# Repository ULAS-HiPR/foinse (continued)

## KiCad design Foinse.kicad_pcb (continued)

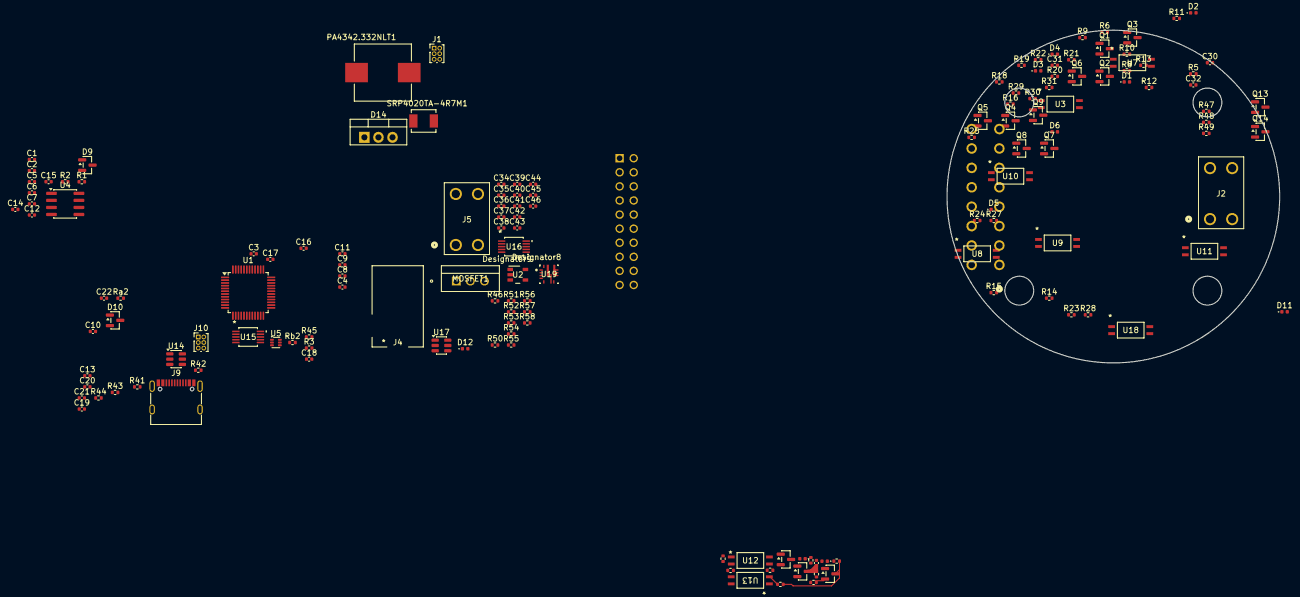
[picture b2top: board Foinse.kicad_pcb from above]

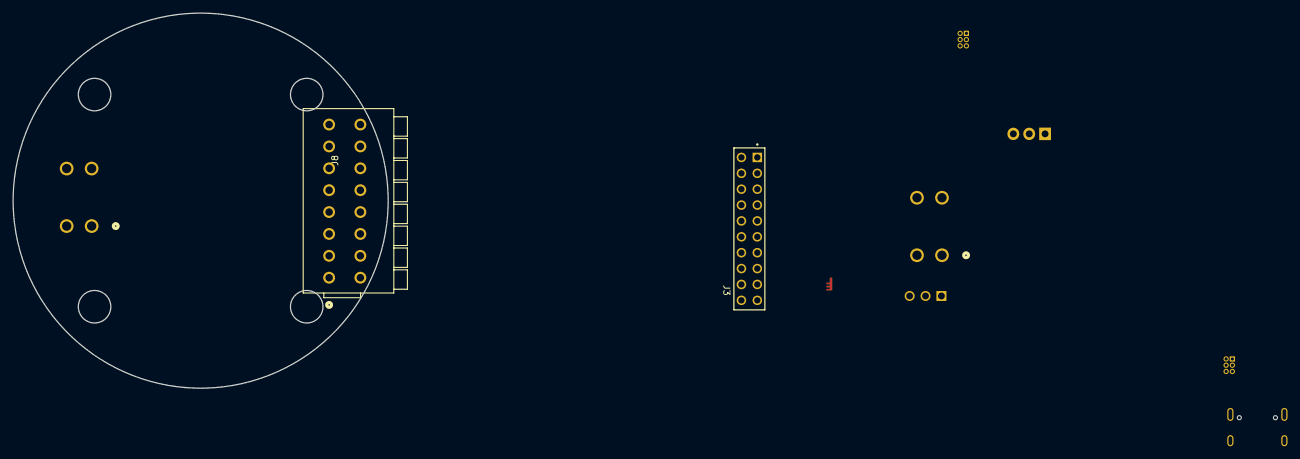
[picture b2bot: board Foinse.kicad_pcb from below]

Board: 4 copper layers, 60.0 x 60.0 mm, 150 parts (2 on the bottom side), 98 nets.

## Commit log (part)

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2026-01-13 inital code import
2026-01-13 inital code import p2
2026-01-13 adding readme
2026-01-14 Added E-Match circuit
2026-01-18 Board V1, before review
2026-01-19 Assighned all footprints
2026-01-20 Fixed shit
2026-01-20 folders are indded cool
2026-01-20 minor changes
2026-01-23 5v logic routed
2026-01-23 new inductor
2026-01-23 new inductor2
2026-01-23 new inductor3
2026-01-23 hehe
2026-01-24 never
2026-01-24 gonna
2026-01-25 give
2026-01-26 can crystal added
2026-01-30 drc pass
2026-02-03 3d models made
2026-02-09 lots to do
2026-02-11 minor stuff
2026-02-17 added voltage sensing
2026-02-17 added voltage sensing3
2026-02-23 ready for review the twost
2026-02-27 ready to go, nearly
2026-03-01 ready 2 order
2026-03-03 removing DS_Store
2026-03-05 Added inital setup w/ default task
2026-03-21 cleaned up component sizes
2026-05-18 feat(sil): update comheadan, linux platform config
